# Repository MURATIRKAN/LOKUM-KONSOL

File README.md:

# LOKUM H1-H2 VE R1-R2-R3 VE R4 ARM LINUX VE ANDROID KONSOL PROJESİ 
MURAT IRKAN 2023-2024 
ANDROID 7.1 OYUN CS-GO: https://play.google.com/store/apps/details?id=com.tlb.csgo.offline&hl=en_GB
----------------------------------------------
MURAT IRKAN 2023-24 https://orangepi.com.tr/destek.html
----------------------------------------------

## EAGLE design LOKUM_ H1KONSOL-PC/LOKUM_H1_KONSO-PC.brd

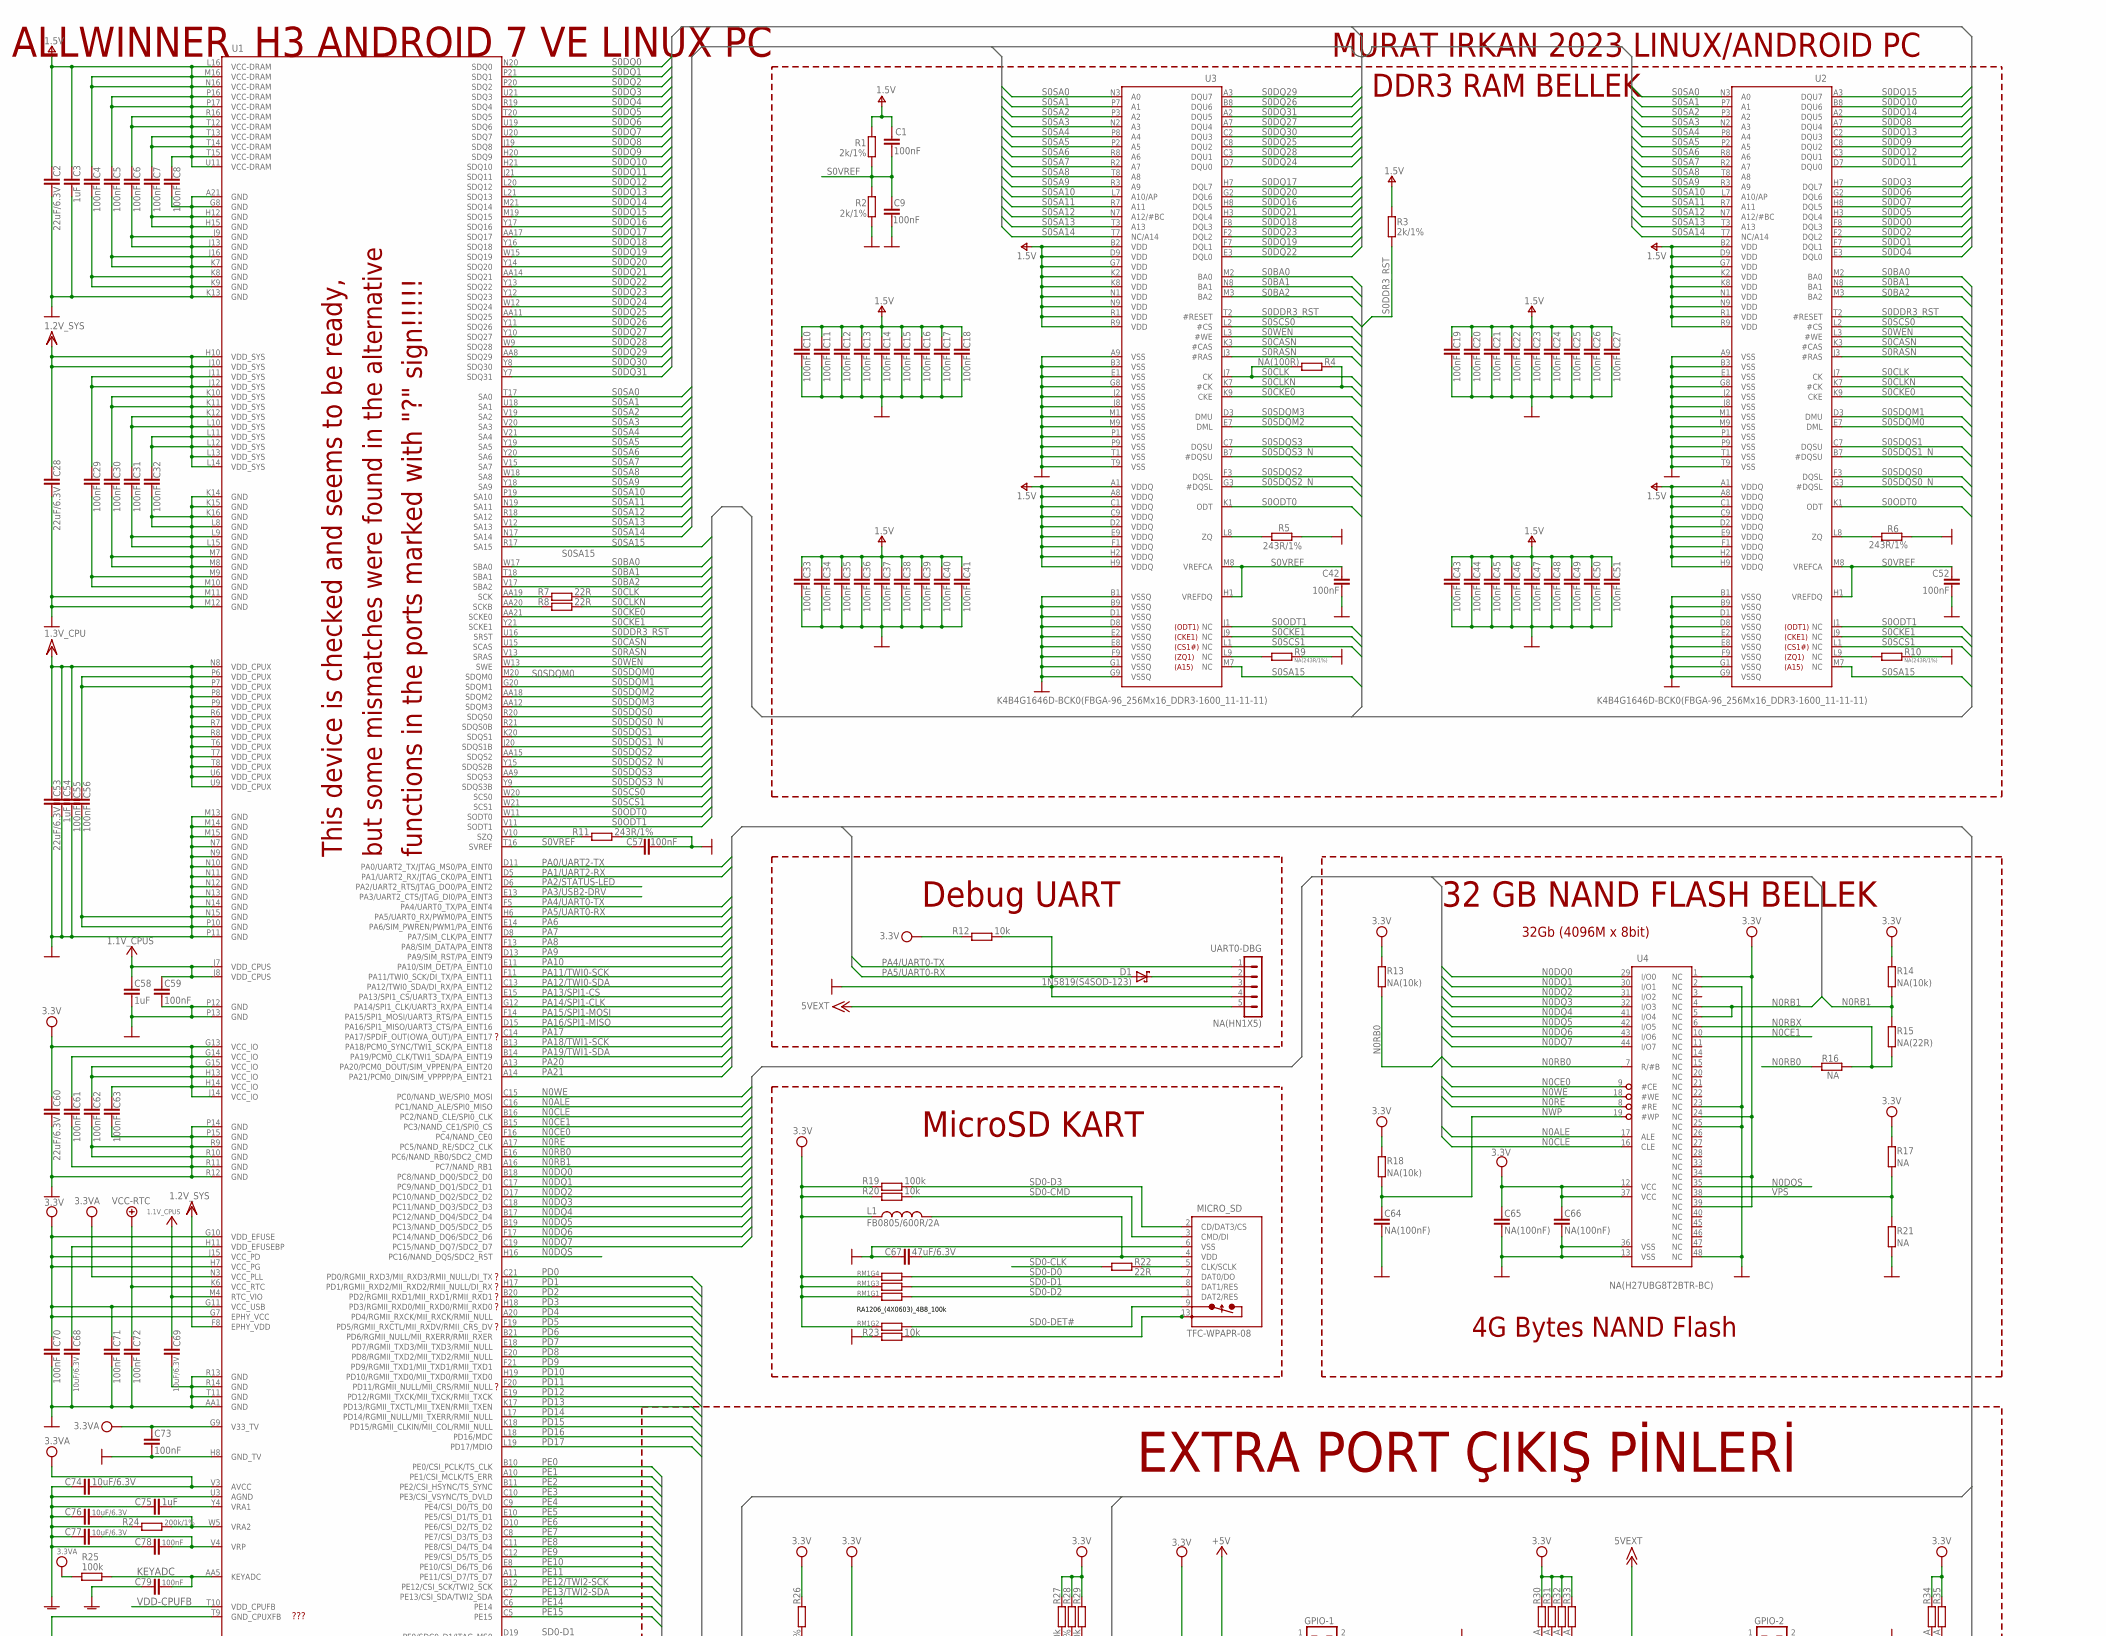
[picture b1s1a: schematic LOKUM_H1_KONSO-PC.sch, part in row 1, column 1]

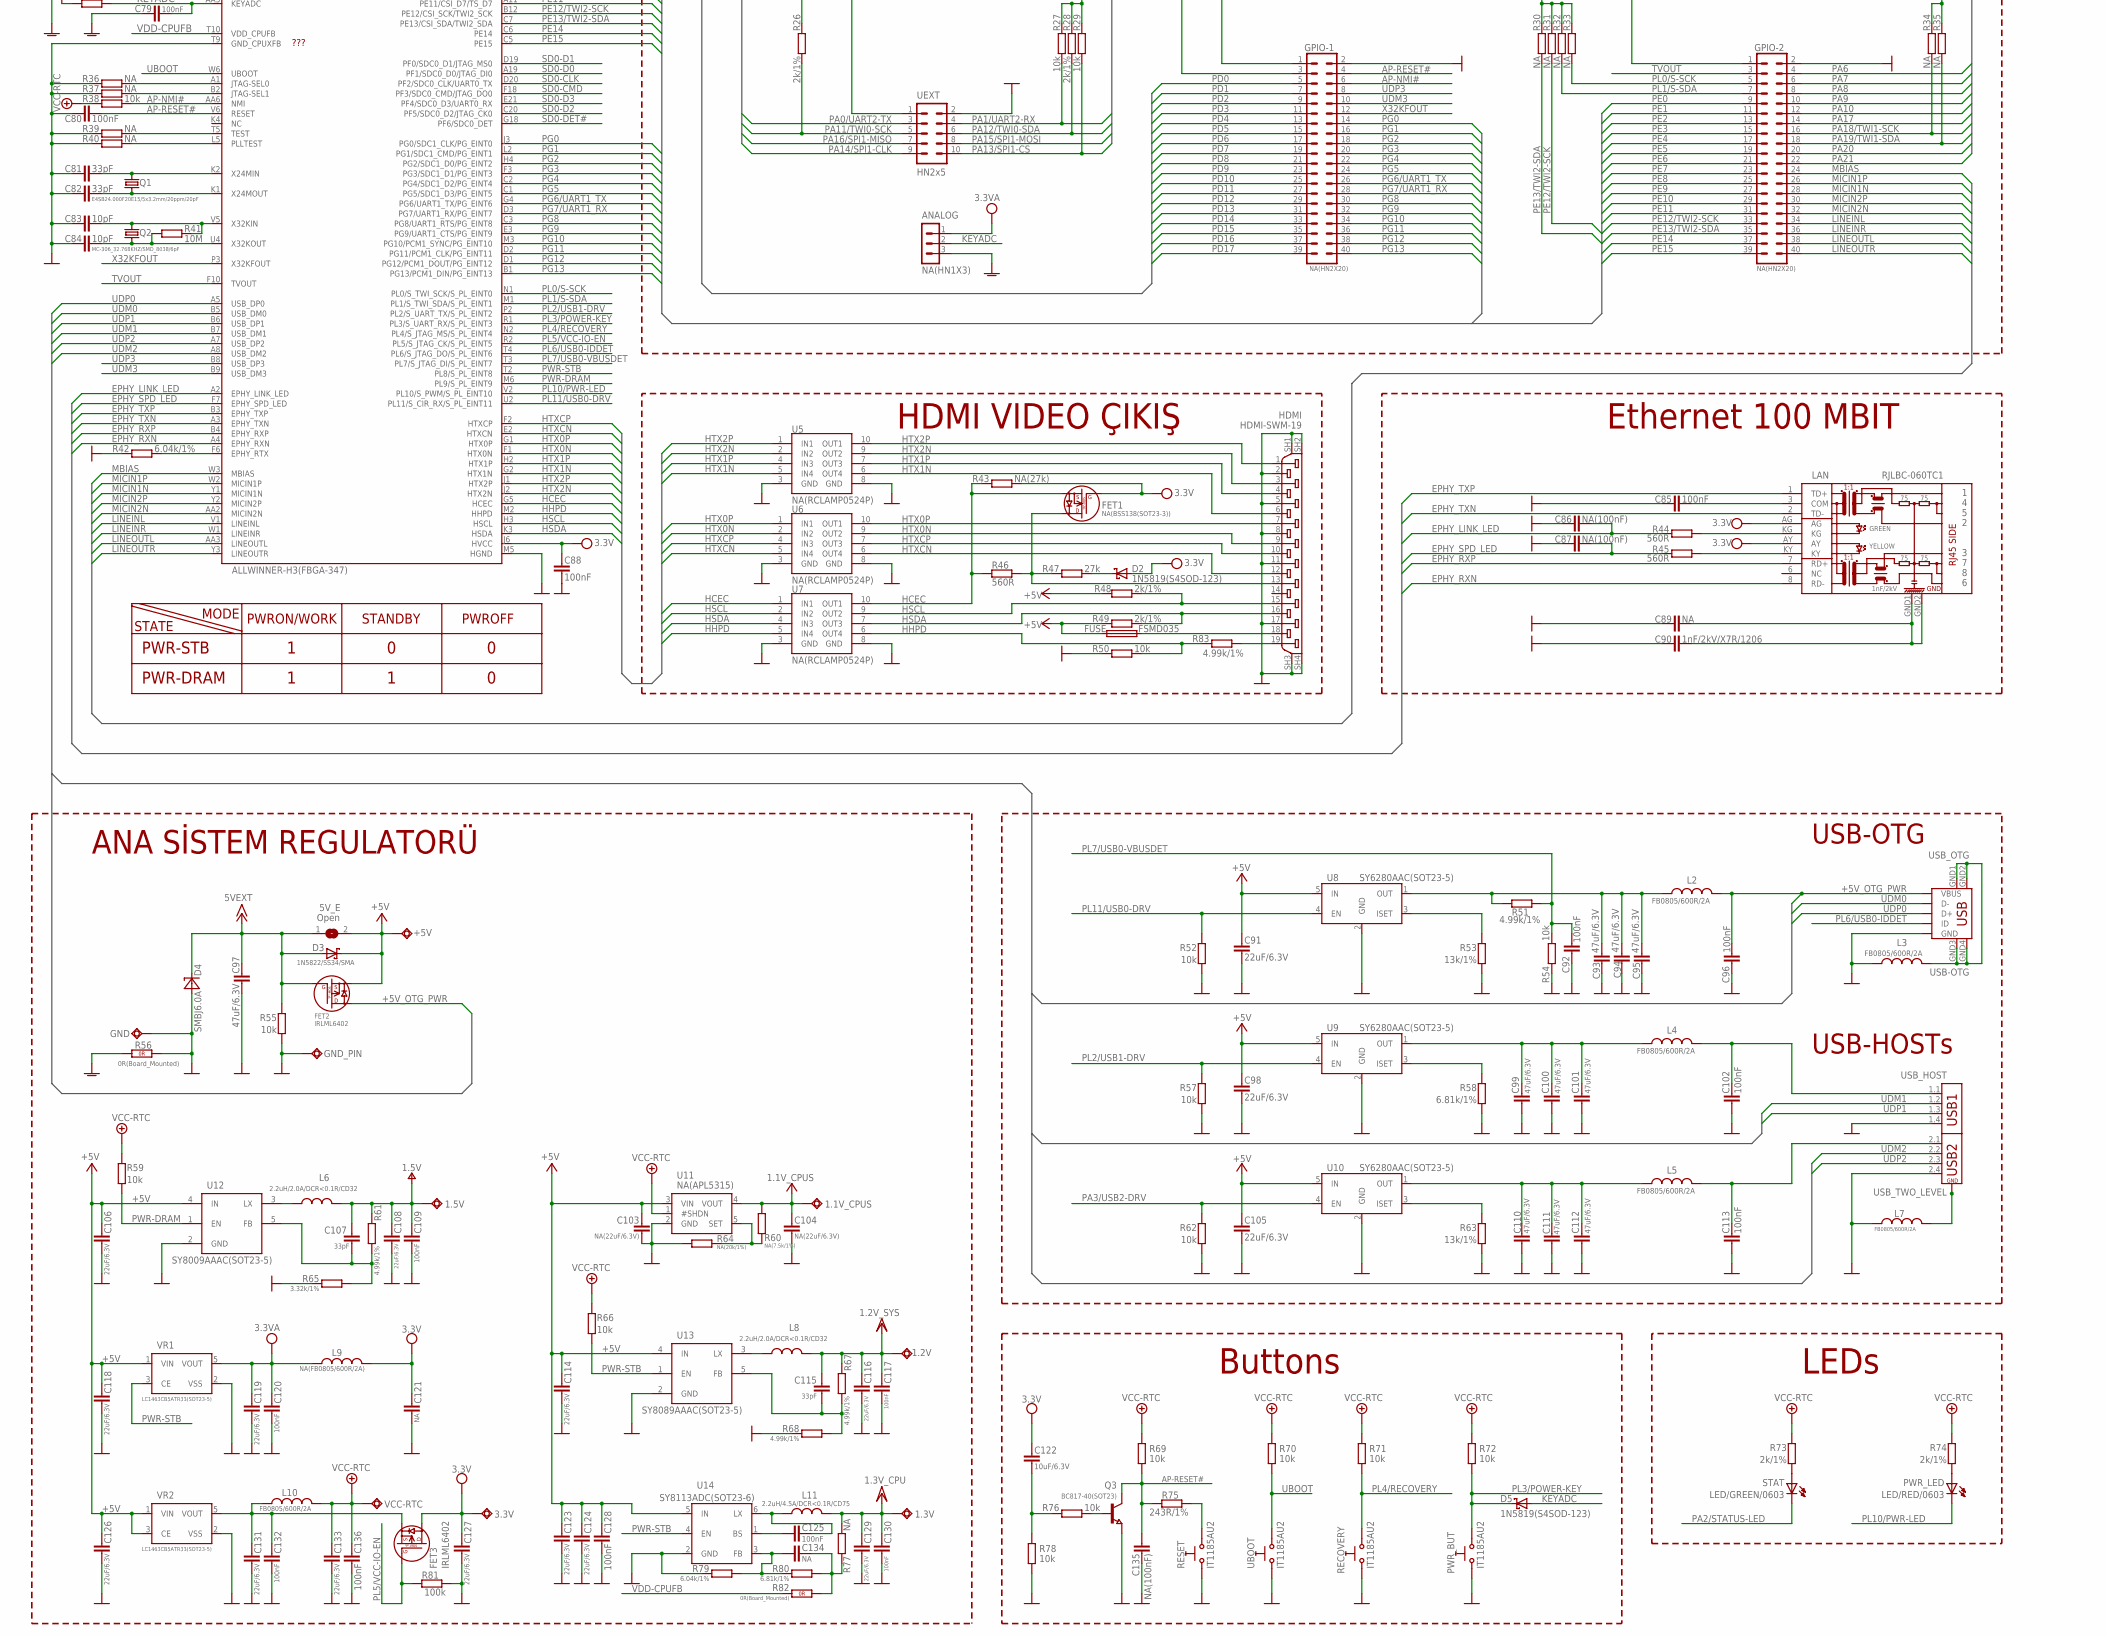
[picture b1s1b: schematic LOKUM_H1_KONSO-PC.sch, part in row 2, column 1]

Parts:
1.1V_CPUS, 1.2V, 1.3V, 1.5V, 3.3V: TESTPADTESTPAD_40-ROUND; TESTPAD_40-ROUND
5V_E: Open; SJ_1_SMALLER
+5V: TESTPADTESTPAD_40-ROUND; TESTPAD_40-ROUND
ANALOG: NA(HN1X3); HN1X3
C1, C4, C5, C6, C7, C8, C9, C10, C11, C12, C13, C14, C15, C16, C17, C18, C19, C20, C21, C22, C23, C24, C25, C26, C27, C29, C30, C31, C32, C33, C34, C35, C36, C37, C38, C39, C40, C41, C42, C43, C44, C45, C46, C47, C48, C49, C50, C51, C52, C55, C56, C57, C59, C61, C62, C63, C70, C71, C72, C73, C78, C79, C80, C85, C88, C92, C96, C102, C109, C113, C117, C120, C125, C128, C130, C132, C136: 100nF; C0402_TI
C2, C28, C53, C60, C91, C98, C105, C106, C108, C114, C116, C118, C119, C123, C124, C126, C127, C129, C131, C133: 22uF/6.3V; C0603_DWS
C3, C54, C58, C75: 1uF; C0603_DWS
C64, C65, C66, C86, C87, C135: NA(100nF); C0402_TI
C67, C93, C94, C95, C97, C99, C100, C101, C110, C111, C112: 47uF/6.3V; C0805_5MIL_DWS
C68, C69, C74, C76, C77, C122: 10uF/6.3V; C0603_DWS
C81, C82, C107, C115: 33pF; C0603_DWS
C83, C84: 10pF; C0603_DWS
C89: NA; C1206_5MILS_WS_ISO
C90: 1nF/2kV/X7R/1206; C1206_5MILS_WS_ISO
C103, C104: NA(22uF/6.3V); C0603_DWS
C121, C134: NA; C0603_DWS
D1, D2, D5: 1N5819(S4SOD-123); SOD-123
D3: 1N5822/SS34/SMA; MLL-41
D4: SMBJ6.0A; DO214AA
FET1: NA(BSS138(SOT23-3)); SOT23
FET2, FET3: IRLML6402; SOT23
FUSE: FSMD035; 1206
GND: TESTPADTESTPAD_40-ROUND; TESTPAD_40-ROUND
GND_PIN: TESTPAD3; TEST_PAD40/70/SQUARE
GPIO-1, GPIO-2: NA(HN2X20); HN2X20-MALE
HDMI: HDMI-SWM-19
L1, L2, L3, L4, L5, L7, L10: FB0805/600R/2A; L0805_5MIL_DWS
L6, L8: 2.2uH/2.0A/DCR<0.1R/CD32; CD32
L9: NA(FB0805/600R/2A); L0805_5MIL_DWS
L11: 2.2uH/4.5A/DCR<0.1R/CD75; CD73(75)
LAN: RJLBC-060TC1; RJLBC-060TC1_MILLING
MICRO_SD: TFC-WPAPR-08
PWR_BUT: IT1185AU2
PWR_LED: LED/RED/0603; LED-0603_TEST
Q1: E4SB24.000F20E15/5x3.2mm/20ppm/20pF; HCX-4S
Q2: MC-306_32.768KHZ/SMD_8038/6pF; MC-306
Q3: BC817-40(SOT23); SOT23
R1, R2, R3, R26, R28, R48, R49, R73, R74: 2k/1%; R0603_5MIL_DWS
R4: NA(100R); R0402_TI
R5, R6, R11, R75: 243R/1%; R0603_5MIL_DWS
R7, R8, R22: 22R; R0402_TI
R9, R10: NA(243R/1%); R0603_5MIL_DWS
R12, R20, R23, R27, R29, R38, R50, R52, R54, R55, R57, R59, R62, R66, R69, R70, R71, R72, R76, R78: 10k; R0603_5MIL_DWS
R13, R14, R18: NA(10k); R0603_5MIL_DWS
R15: NA(22R); R0402_TI
R16, R17, R21, R30, R31, R32, R33, R34, R35, R36, R37, R39, R40, R77: NA; R0603_5MIL_DWS
R19, R25, R81: 100k; R0603_5MIL_DWS
R24: 200k/1%; R0603_5MIL_DWS
R41: 10M; R0603_5MIL_DWS
R42, R79: 6.04k/1%; R0603_5MIL_DWS
R43: NA(27k); R0603_5MIL_DWS
R44, R45, R46: 560R; R0603_5MIL_DWS
R47: 27k; R0603_5MIL_DWS
R51, R61, R67, R68, R83: 4.99k/1%; R0603_5MIL_DWS
R53, R63: 13k/1%; R0603_5MIL_DWS
R56, R82: 0R(Board_Mounted); 0603_0R
R58, R80: 6.81k/1%; R0603_5MIL_DWS
R60: NA(7.5k/1%); R0603_5MIL_DWS
R64: NA(20k/1%); R0603_5MIL_DWS
R65: 3.32k/1%; R0603_5MIL_DWS
RECOVERY: IT1185AU2
RESET: IT1185AU2
RM1: RA1206_(4X0603)_4B8_100k; R_MATRIX_4
STAT: LED/GREEN/0603; LED-0603_TEST
U1: ALLWINNER-H3(FBGA-347); FBGA-347
U2, U3: K4B4G1646D-BCK0(FBGA-96_256Mx16_DDR3-1600_11-11-1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; FBGA96(HYNIX_SAMSUNG_512MX16_DDR3)
U4: NA(H27UBG8T2BTR-BC); TSOP48
U5, U6, U7: NA(RCLAMP0524P); SLP2510P8
U8, U9, U10: SY6280AAC(SOT23-5); SOT23-5
U11: NA(APL5315); SOT-23-5
U12: SY8009AAAC(SOT23-5); SOT23-5
U13: SY8089AAAC(SOT23-5); SOT23-5
U14: SY8113ADC(SOT23-6); SOT23-6
UART0-DBG: NA(HN1X5); HN1X5
UBOOT: IT1185AU2
UEXT: HN2x5; ML10_NEW
USB_HOST: USB_TWO_LEVEL
USB_OTG: USB-OTG; USB_MINI_9PIN
VCC-RTC: TESTPADTESTPAD_40-ROUND; TESTPAD_40-ROUND
VR1, VR2: LC1463CB5ATR33(SOT23-5); SOT-23-5

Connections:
+5V: 5V_E.2, +5V.1, C91.1, C98.1, C103.1, C105.1, C106.1, C114.1, C118.1, C123.1, C124.1, C126.1, C128.2, D3.K (C), FET2.2 (S), FUSE.1, GPIO-1.1, R48.2, R49.2, U8.5 (IN), U9.5 (IN), U10.5 (IN), U11.3 (VIN), U12.4 (IN), U13.4 (IN), U14.5 (IN), VR1.1 (VIN), VR2.1 (VIN), VR2.3 (CE)
+5V_OTG_PWR: C96.1, FET2.3 (D), L2.1, USB_OTG.VBUS
+7V: C72.2, C133.1, C136.2, L10.2, R38.2, R59.1, R66.1, R69.1, R70.1, R71.1, R72.1, R73.1, R74.1, U1.K6 (VCC_RTC), U11.1 (#SHDN), VCC-RTC.1
+15V: 5V_E.1, C97.1, D3.A, D4.C, FET2.1 (G), GPIO-2.1, R55.2, UART0-DBG.5
AP-NMI#: GPIO-1.6, R38.1, U1.AA6 (NMI)
AP-RESET#: C80.2, C135.2, GPIO-1.4, Q3.3 (C), R69.2, R75.2, U1.V6 (RESET)
EPHY_LINK_LED: C86.2, R44.2, U1.A2 (EPHY_LINK_LED)
EPHY_RXN: LAN.8 (RD-), U1.A4 (EPHY_RXN)
EPHY_RXP: LAN.7 (RD+), U1.B4 (EPHY_RXP)
EPHY_SPD_LED: C87.2, R45.2, U1.F7 (EPHY_SPD_LED)
EPHY_TXN: LAN.2 (TD-), U1.A3 (EPHY_TXN)
EPHY_TXP: LAN.1 (TD+), U1.B3 (EPHY_TXP)
GND: C2.2, C3.2, C4.1, C5.1, C6.1, C7.1, C8.1, C9.1, C10.1, C11.1, C12.1, C13.1, C14.1, C15.1, C16.1, C17.1, C18.1, C19.1, C20.1, C21.1, C22.1, C23.1, C24.1, C25.1, C26.1, C27.1, C28.2, C29.1, C30.1, C31.1, C32.1, C33.1, C34.1, C35.1, C36.1, C37.1, C38.1, C39.1, C40.1, C41.1, C42.1, C43.1, C44.1, C45.1, C46.1, C47.1, C48.1, C49.1, C50.1, C51.1, C52.1, C53.2, C54.2, C55.1, C56.1, C57.1, C58.2, C59.1, C60.2, C61.1, C62.1, C63.1, C64.1, C65.1, C66.1, C67.1, C68.2, C69.2, C70.1, C71.1, C72.1, C73.1, C80.1, C81.1, C82.1, C83.1, C84.1, C85.1, C86.1, C87.1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
GNDA: ANALOG.3, C74.1, C75.1, C76.1, C77.1, C78.1, C79.1, R24.2, R56.2 (1.2), U1.U3 (AGND)
HCEC: FET1.2 (S), R43.1, R46.2, U1.G5 (HCEC), U7.1 (IN1), U7.10 (OUT1)
HDMI_5V_SOURCE: FUSE.2, HDMI.18
HHPD: R50.1, R83.1, U1.M2 (HHPD), U7.5 (IN4), U7.6 (OUT4)
HSCL: HDMI.15, R48.1, U1.H3 (HSCL), U7.2 (IN2), U7.9 (OUT2)
HSDA: HDMI.16, R49.1, U1.K3 (HSDA), U7.4 (IN3), U7.7 (OUT3)
HTX0N: HDMI.9, U1.F1 (HTX0N), U6.2 (IN2), U6.9 (OUT2)
HTX0P: HDMI.7, U1.G1 (HTX0P), U6.1 (IN1), U6.10 (OUT1)
HTX1N: HDMI.6, U1.G2 (HTX1N), U5.5 (IN4), U5.6 (OUT4)
HTX1P: HDMI.4, U1.H2 (HTX1P), U5.4 (IN3), U5.7 (OUT3)
HTX2N: HDMI.3, U1.J2 (HTX2N), U5.2 (IN2), U5.9 (OUT2)
HTX2P: HDMI.1, U1.J1 (HTX2P), U5.1 (IN1), U5.10 (OUT1)
HTXCN: HDMI.12, U1.E2 (HTXCN), U6.5 (IN4), U6.6 (OUT4)
HTXCP: HDMI.10, U1.F2 (HTXCP), U6.4 (IN3), U6.7 (OUT3)
KEYADC: ANALOG.2, C79.2, D5.A, R25.1, U1.AA5 (KEYADC)
LINEINL: GPIO-2.34, U1.V1 (LINEINL)
LINEINR: GPIO-2.36, U1.W1 (LINEINR)
LINEOUTL: GPIO-2.38, U1.AA3 (LINEOUTL)
LINEOUTR: GPIO-2.40, U1.Y3 (LINEOUTR)
MBIAS: GPIO-2.24, U1.W3 (MBIAS)
MICIN1N: GPIO-2.28, U1.Y1 (MICIN1N)
MICIN1P: GPIO-2.26, U1.W2 (MICIN1P)
MICIN2N: GPIO-2.32, U1.AA2 (MICIN2N)
MICIN2P: GPIO-2.30, U1.Y2 (MICIN2P)
N0ALE: U1.C16 (PC1/NAND_ALE/SPI0_MISO), U4.17 (ALE)
N0CE0: U1.F16 (PC4/NAND_CE0), U4.9 (#CE)
N0CE1: U1.B15 (PC3/NAND_CE1/SPI0_CS), U4.10 (NC)
N0CLE: U1.B16 (PC2/NAND_CLE/SPI0_CLK), U4.16 (CLE)
N0DQ0: U1.B18 (PC8/NAND_DQ0/SDC2_D0), U4.29 (I/O0)
N0DQ1: U1.C17 (PC9/NAND_DQ1/SDC2_D1), U4.30 (I/O1)
N0DQ2: U1.D17 (PC10/NAND_DQ2/SDC2_D2), U4.31 (I/O2)
N0DQ3: U1.C18 (PC11/NAND_DQ3/SDC2_D3), U4.32 (I/O3)
N0DQ4: U1.B17 (PC12/NAND_DQ4/SDC2_D4), U4.41 (I/O4)
N0DQ5: U1.B19 (PC13/NAND_DQ5/SDC2_D5), U4.42 (I/O5)
N0DQ6: U1.F17 (PC14/NAND_DQ6/SDC2_D6), U4.43 (I/O6)
N0DQ7: U1.C19 (PC15/NAND_DQ7/SDC2_D7), U4.44 (I/O7)
N0DQS: U1.H16 (PC16/NAND_DQS/SDC2_RST), U4.35 (NC)
N0RB0: R13.2, R16.2, U1.E16 (PC6/NAND_RB0/SDC2_CMD), U4.7 (R/#B)
N0RB1: R14.2, R15.1, U1.A16 (PC7/NAND_RB1), U4.4 (NC), U4.5 (NC)
N0RBX: R15.2, R16.1, U4.6 (NC)
N0RE: U1.A17 (PC5/NAND_RE/SDC2_CLK), U4.8 (#RE)
N0WE: U1.C15 (PC0/NAND_WE/SPI0_MOSI), U4.18 (#WE)
unnamed: MICRO_SD.5 (CLK/SCLK), R22.1
unnamed: R11.2, U1.V10 (SZQ)
unnamed: R5.2, U3.L8 (ZQ)
unnamed: D2.C, R47.1
unnamed: R6.2, U2.L8 (ZQ)
unnamed: R9.2, U3.L9 (NC)
unnamed: D1.C, UART0-DBG.2
unnamed: R7.2, U1.AA19 (SCK)
unnamed: R8.2, U1.AA20 (SCKB)
unnamed: R37.1, U1.B2 (JTAG-SEL1)
unnamed: R10.2, U2.L9 (NC)
unnamed: L3.2, USB_OTG.GND1, USB_OTG.GND2, USB_OTG.GND3, USB_OTG.GND4
unnamed: HDMI.19, R83.2
unnamed: C75.2, U1.Y4 (VRA1)
unnamed: R53.2, U8.3 (ISET)
unnamed: R75.1, RESET.1 (0)
unnamed: C93.1, C94.1, C95.1, L2.2, R51.2, U8.1 (OUT)
unnamed: FET1.3 (D), HDMI.13, R46.1, R47.2
unnamed: Q3.1 (B), R76.2
unnamed: C89.2, C90.2, LAN.GND1, LAN.GND2
unnamed: L6.1, U12.3 (LX)
unnamed: R36.1, U1.A1 (JTAG-SEL0)
unnamed: R39.1, U1.T5 (TEST)
unnamed: R60.2, R64.2, U11.5 (SET)
unnamed: R40.1, U1.L5 (PLLTEST)
unnamed: C107.2, R61.2, R65.1, U12.5 (FB)
unnamed: C122.2, R76.1, R78.1
unnamed: C125.2, U14.1 (BS)
unnamed: L8.1, U13.3 (LX)
unnamed: C115.2, R67.2, R68.1, U13.5 (FB)
unnamed: C125.1, L11.1, U14.6 (LX)
unnamed: PWR_LED.A, R74.2
unnamed: C134.2, R79.1, R80.1, U14.3 (FB)
unnamed: LAN.KG, R44.1
unnamed: R42.1, U1.F6 (EPHY_RTX)
unnamed: C85.2, LAN.3 (COM)
unnamed: LAN.KY, R45.1
unnamed: MICRO_SD.10 (PACK1), MICRO_SD.11 (PACK2), MICRO_SD.12 (PACK3), MICRO_SD.13 (PACK4), R23.1
unnamed: C131.1, C132.1, FET3.2 (S), L10.1, VR2.5 (VOUT)
unnamed: C83.2, Q2.4 (2), R41.1, U1.V5 (X32KIN)
unnamed: R58.2, U9.3 (ISET)
unnamed: C102.1, L4.2, USB_HOST.1.1
unnamed: C84.2, Q2.1, R41.2, U1.U4 (X32KOUT)
unnamed: C77.2, C78.2, U1.V4 (VRP)
unnamed: R63.2, U10.3 (ISET)
unnamed: C76.2, R24.1, U1.W5 (VRA2)
unnamed: C99.1, C100.1, C101.1, L4.1, U9.1 (OUT)
unnamed: L7.2, USB_HOST.GND1, USB_HOST.GND2, USB_HOST.GND3, USB_HOST.GND4
unnamed: C113.1, L5.2, USB_HOST.2.1
unnamed: C110.1, C111.1, C112.1, L5.1, U10.1 (OUT)
unnamed: R73.2, STAT.A
NWP: C64.2, R18.2, U4.19 (#WP)
PA0/UART2-TX: U1.D11 (PA0/UART2_TX/JTAG_MS0/PA_EINT0), UEXT.3
PA1/UART2-RX: R27.2, U1.D5 (PA1/UART2_RX/JTAG_CK0/PA_EINT1), UEXT.4
PA2/STATUS-LED: STAT.C, U1.D6 (PA2/UART2_RTS/JTAG_DO0/PA_EINT2)
PA3/USB2-DRV: R62.2, U1.E13 (PA3/UART2_CTS/JTAG_DI0/PA_EINT3), U10.4 (EN)
PA4/UART0-TX: U1.F5 (PA4/UART0_TX/PA_EINT4), UART0-DBG.1
PA5/UART0-RX: D1.A, R12.1, U1.H6 (PA5/UART0_RX/PWM0/PA_EINT5)
PA6: GPIO-2.4, U1.E14 (PA6/SIM_PWREN/PWM1/PA_EINT6)
PA7: GPIO-2.6, U1.D8 (PA7/SIM_CLK/PA_EINT7)
PA8: GPIO-2.8, U1.F13 (PA8/SIM_DATA/PA_EINT8)
PA9: GPIO-2.10, U1.D13 (PA9/SIM_RST/PA_EINT9)
PA10: GPIO-2.12, U1.E11 (PA10/SIM_DET/PA_EINT10)
PA11/TWI0-SCK: R26.2, U1.F11 (PA11/TWI0_SCK/DI_TX/PA_EINT11), UEXT.5
PA12/TWI0-SDA: R28.2, U1.C13 (PA12/TWI0_SDA/DI_RX/PA_EINT12), UEXT.6
PA13/SPI1-CS: R29.2, U1.E15 (PA13/SPI1_CS/UART3_TX/PA_EINT13), UEXT.10
PA14/SPI1-CLK: U1.G12 (PA14/SPI1_CLK/UART3_RX/PA_EINT14), UEXT.9
PA15/SPI1-MOSI: U1.F14 (PA15/SPI1_MOSI/UART3_RTS/PA_EINT15), UEXT.8
PA16/SPI1-MISO: U1.D15 (PA16/SPI1_MISO/UART3_CTS/PA_EINT16), UEXT.7
PA17: GPIO-2.14, U1.C14 (PA17/SPDIF_OUT(OWA_OUT)/PA_EINT17)
PA18/TWI1-SCK: GPIO-2.16, R34.2, U1.B13 (PA18/PCM0_SYNC/TWI1_SCK/PA_EINT18)
PA19/TWI1-SDA: GPIO-2.18, R35.2, U1.B14 (PA19/PCM0_CLK/TWI1_SDA/PA_EINT19)
PA20: GPIO-2.20, U1.A13 (PA20/PCM0_DOUT/SIM_VPPEN/PA_EINT20)
PA21: GPIO-2.22, U1.A14 (PA21/PCM0_DIN/SIM_VPPPP/PA_EINT21)
PD0: GPIO-1.5, U1.C21 (PD0/RGMII_RXD3/MII_RXD3/RMII_NULL/DI_TX)
PD1: GPIO-1.7, U1.H17 (PD1/RGMII_RXD2/MII_RXD2/RMII_NULL/DI_RX)
PD2: GPIO-1.9, U1.B20 (PD2/RGMII_RXD1/MII_RXD1/RMII_RXD1)
PD3: GPIO-1.11, U1.H18 (PD3/RGMII_RXD0/MII_RXD0/RMII_RXD0)
PD4: GPIO-1.13, U1.A20 (PD4/RGMII_RXCK/MII_RXCK/RMII_NULL)
PD5: GPIO-1.15, U1.F19 (PD5/RGMII_RXCTL/MII_RXDV/RMII_CRS_DV)
PD6: GPIO-1.17, U1.B21 (PD6/RGMII_NULL/MII_RXERR/RMII_RXER)
PD7: GPIO-1.19, U1.E18 (PD7/RGMII_TXD3/MII_TXD3/RMII_NULL)
PD8: GPIO-1.21, U1.E20 (PD8/RGMII_TXD2/MII_TXD2/RMII_NULL)
PD9: GPIO-1.23, U1.F21 (PD9/RGMII_TXD1/MII_TXD1/RMII_TXD1)
PD10: GPIO-1.25, U1.H19 (PD10/RGMII_TXD0/MII_TXD0/RMII_TXD0)
PD11: GPIO-1.27, U1.F20 (PD11/RGMII_NULL/MII_CRS/RMII_NULL)
PD12: GPIO-1.29, U1.E19 (PD12/RGMII_TXCK/MII_TXCK/RMII_TXCK)
PD13: GPIO-1.31, U1.K17 (PD13/RGMII_TXCTL/MII_TXEN/RMII_TXEN)
PD14: GPIO-1.33, U1.L17 (PD14/RGMII_NULL/MII_TXERR/RMII_NULL)
PD15: GPIO-1.35, U1.K18 (PD15/RGMII_CLKIN/MII_COL/RMII_NULL)
PD16: GPIO-1.37, U1.L18 (PD16/MDC)
PD17: GPIO-1.39, U1.L19 (PD17/MDIO)
PE0: GPIO-2.9, U1.B10 (PE0/CSI_PCLK/TS_CLK)
PE1: GPIO-2.11, U1.A10 (PE1/CSI_MCLK/TS_ERR)
PE2: GPIO-2.13, U1.B11 (PE2/CSI_HSYNC/TS_SYNC)
PE3: GPIO-2.15, U1.C10 (PE3/CSI_VSYNC/TS_DVLD)
PE4: GPIO-2.17, U1.C9 (PE4/CSI_D0/TS_D0)
PE5: GPIO-2.19, U1.E10 (PE5/CSI_D1/TS_D1)
PE6: GPIO-2.21, U1.D10 (PE6/CSI_D2/TS_D2)
PE7: GPIO-2.23, U1.C8 (PE7/CSI_D3/TS_D3)
PE8: GPIO-2.25, U1.C11 (PE8/CSI_D4/TS_D4)
PE9: GPIO-2.27, U1.C12 (PE9/CSI_D5/TS_D5)
PE10: GPIO-2.29, U1.E8 (PE10/CSI_D6/TS_D6)
PE11: GPIO-2.31, U1.A11 (PE11/CSI_D7/TS_D7)
PE12/TWI2-SCK: GPIO-2.33, R31.2, U1.B12 (PE12/CSI_SCK/TWI2_SCK)
PE13/TWI2-SDA: GPIO-2.35, R30.2, U1.C7 (PE13/CSI_SDA/TWI2_SDA)
PE14: GPIO-2.37, U1.C6 (PE14)
PE15: GPIO-2.39, U1.C5 (PE15)
PG0: GPIO-1.14, U1.J3 (PG0/SDC1_CLK/PG_EINT0)
PG1: GPIO-1.16, U1.L2 (PG1/SDC1_CMD/PG_EINT1)
PG2: GPIO-1.18, U1.H4 (PG2/SDC1_D0/PG_EINT2)
PG3: GPIO-1.20, U1.F3 (PG3/SDC1_D1/PG_EINT3)
PG4: GPIO-1.22, U1.C2 (PG4/SDC1_D2/PG_EINT4)
PG5: GPIO-1.24, U1.C1 (PG5/SDC1_D3/PG_EINT5)
PG6/UART1_TX: GPIO-1.26, U1.G4 (PG6/UART1_TX/PG_EINT6)
PG7/UART1_RX: GPIO-1.28, U1.D3 (PG7/UART1_RX/PG_EINT7)
PG8: GPIO-1.30, U1.C3 (PG8/UART1_RTS/PG_EINT8)
PG9: GPIO-1.32, U1.E3 (PG9/UART1_CTS/PG_EINT9)
PG10: GPIO-1.34, U1.M3 (PG10/PCM1_SYNC/PG_EINT10)
PG11: GPIO-1.36, U1.D2 (PG11/PCM1_CLK/PG_EINT11)
PG12: GPIO-1.38, U1.D1 (PG12/PCM1_DOUT/PG_EINT12)
PG13: GPIO-1.40, U1.B1 (PG13/PCM1_DIN/PG_EINT13)
PL0/S-SCK: GPIO-2.5, R33.2, U1.N1 (PL0/S_TWI_SCK/S_PL_EINT0)
PL1/S-SDA: GPIO-2.7, R32.2, U1.M1 (PL1/S_TWI_SDA/S_PL_EINT1)
PL2/USB1-DRV: R57.2, U1.P2 (PL2/S_UART_TX/S_PL_EINT2), U9.4 (EN)
PL3/POWER-KEY: D5.C, PWR_BUT.1 (0), R72.2, U1.R1 (PL3/S_UART_RX/S_PL_EINT3)
PL4/RECOVERY: R71.2, RECOVERY.1 (0), U1.N2 (PL4/S_JTAG_MS/S_PL_EINT4)
PL5/VCC-IO-EN: FET3.1 (G), R81.1, U1.R2 (PL5/S_JTAG_CK/S_PL_EINT5)
PL6/USB0-IDDET: U1.T4 (PL6/S_JTAG_DO/S_PL_EINT6), USB_OTG.ID
PL7/USB0-VBUSDET: C92.1, R51.1, R54.2, U1.T3 (PL7/S_JTAG_DI/S_PL_EINT7)
PL10/PWR-LED: PWR_LED.C, U1.V2 (PL10/S_PWM/S_PL_EINT10)
PL11/USB0-DRV: R52.2, U1.U2 (PL11/S_CIR_RX/S_PL_EINT11), U8.4 (EN)
PWR-DRAM: R59.2, U1.M6 (PL9/S_PL_EINT9), U12.1 (EN)
PWR-STB: R66.2, U1.T2 (PL8/S_PL_EINT8), U13.1 (EN), U14.4 (EN), VR1.3 (CE)
S0BA0: U1.W17 (SBA0), U2.M2 (BA0), U3.M2 (BA0)
S0BA1: U1.T18 (SBA1), U2.N8 (BA1), U3.N8 (BA1)
S0BA2: U1.V17 (SBA2), U2.M3 (BA2), U3.M3 (BA2)
S0CASN: U1.U15 (SCAS), U2.K3 (#CAS), U3.K3 (#CAS)
S0CKE0: U1.AA21 (SCKE0), U2.K9 (CKE), U3.K9 (CKE)
S0CKE1: U1.Y21 (SCKE1), U2.J9 (NC), U3.J9 (NC)
S0CLK: R4.2, R7.1, U2.J7 (CK), U3.J7 (CK)
S0CLKN: R4.1, R8.1, U2.K7 (#CK), U3.K7 (#CK)
S0DDR3_RST: R3.1, U1.U16 (SRST), U2.T2 (#RESET), U3.T2 (#RESET)
S0DQ0: U1.N20 (SDQ0), U2.F8 (DQL3)
S0DQ1: U1.P21 (SDQ1), U2.F7 (DQL1)
S0DQ2: U1.P20 (SDQ2), U2.F2 (DQL2)
S0DQ3: U1.U21 (SDQ3), U2.H7 (DQL7)
S0DQ4: U1.R19 (SDQ4), U2.E3 (DQL0)
S0DQ5: U1.T20 (SDQ5), U2.H3 (DQL4)
S0DQ6: U1.U19 (SDQ6), U2.G2 (DQL6)
S0DQ7: U1.U20 (SDQ7), U2.H8 (DQL5)
S0DQ8: U1.J19 (SDQ8), U2.A7 (DQU4)
S0DQ9: U1.H20 (SDQ9), U2.C8 (DQU2)
S0DQ10: U1.H21 (SDQ10), U2.B8 (DQU6)
S0DQ11: U1.J21 (SDQ11), U2.D7 (DQU0)
S0DQ12: U1.L20 (SDQ12), U2.C3 (DQU1)
S0DQ13: U1.L21 (SDQ13), U2.C2 (DQU3)
S0DQ14: U1.M21 (SDQ14), U2.A2 (DQU5)
S0DQ15: U1.M19 (SDQ15), U2.A3 (DQU7)
S0DQ16: U1.Y17 (SDQ16), U3.H8 (DQL5)
S0DQ17: U1.AA17 (SDQ17), U3.H7 (DQL7)
S0DQ18: U1.Y16 (SDQ18), U3.F8 (DQL3)
S0DQ19: U1.W15 (SDQ19), U3.F7 (DQL1)
S0DQ20: U1.Y14 (SDQ20), U3.G2 (DQL6)
S0DQ21: U1.AA14 (SDQ21), U3.H3 (DQL4)
S0DQ22: U1.Y13 (SDQ22), U3.E3 (DQL0)
S0DQ23: U1.Y12 (SDQ23), U3.F2 (DQL2)
S0DQ24: U1.W12 (SDQ24), U3.D7 (DQU0)
S0DQ25: U1.AA11 (SDQ25), U3.C8 (DQU2)
S0DQ26: U1.Y11 (SDQ26), U3.B8 (DQU6)
S0DQ27: U1.Y10 (SDQ27), U3.A7 (DQU4)
S0DQ28: U1.W9 (SDQ28), U3.C3 (DQU1)
S0DQ29: U1.AA8 (SDQ29), U3.A3 (DQU7)
S0DQ30: U1.Y8 (SDQ30), U3.C2 (DQU3)
S0DQ31: U1.Y7 (SDQ31), U3.A2 (DQU5)
S0ODT0: U1.W11 (SODT0), U2.K1 (ODT), U3.K1 (ODT)
S0ODT1: U1.V11 (SODT1), U2.J1 (NC), U3.J1 (NC)
S0RASN: U1.V13 (SRAS), U2.J3 (#RAS), U3.J3 (#RAS)
S0SA0: U1.T17 (SA0), U2.N3 (A0), U3.N3 (A0)
S0SA1: U1.U18 (SA1), U2.P7 (A1), U3.P7 (A1)
S0SA2: U1.V19 (SA2), U2.P3 (A2), U3.P3 (A2)
S0SA3: U1.V20 (SA3), U2.N2 (A3), U3.N2 (A3)
S0SA4: U1.V21 (SA4), U2.P8 (A4), U3.P8 (A4)
S0SA5: U1.Y19 (SA5), U2.P2 (A5), U3.P2 (A5)
S0SA6: U1.Y20 (SA6), U2.R8 (A6), U3.R8 (A6)
S0SA7: U1.V15 (SA7), U2.R2 (A7), U3.R2 (A7)
S0SA8: U1.W18 (SA8), U2.T8 (A8), U3.T8 (A8)
S0SA9: U1.Y18 (SA9), U2.R3 (A9), U3.R3 (A9)
S0SA10: U1.P19 (SA10), U2.L7 (A10/AP), U3.L7 (A10/AP)
S0SA11: U1.N19 (SA11), U2.R7 (A11), U3.R7 (A11)
S0SA12: U1.R18 (SA12), U2.N7 (A12/#BC), U3.N7 (A12/#BC)
S0SA13: U1.V12 (SA13), U2.T3 (A13), U3.T3 (A13)
S0SA14: U1.N17 (SA14), U2.T7 (NC/A14), U3.T7 (NC/A14)
S0SA15: U1.R17 (SA15), U2.M7 (NC), U3.M7 (NC)
S0SCS0: U1.W20 (SCS0), U2.L2 (#CS), U3.L2 (#CS)
S0SCS1: U1.W21 (SCS1), U2.L1 (NC), U3.L1 (NC)
S0SDQM0: U1.M20 (SDQM0), U2.E7 (DML)
S0SDQM1: U1.G20 (SDQM1), U2.D3 (DMU)
S0SDQM2: U1.AA18 (SDQM2), U3.E7 (DML)
S0SDQM3: U1.AA12 (SDQM3), U3.D3 (DMU)
S0SDQS0: U1.R20 (SDQS0), U2.F3 (DQSL)
S0SDQS0_N: U1.R21 (SDQS0B), U2.G3 (#DQSL)
S0SDQS1: U1.K20 (SDQS1), U2.C7 (DQSU)
S0SDQS1_N: U1.J20 (SDQS1B), U2.B7 (#DQSU)
S0SDQS2: U1.AA15 (SDQS2), U3.F3 (DQSL)
S0SDQS2_N: U1.Y15 (SDQS2B), U3.G3 (#DQSL)
S0SDQS3: U1.AA9 (SDQS3), U3.C7 (DQSU)
S0SDQS3_N: U1.Y9 (SDQS3B), U3.B7 (#DQSU)
S0VREF: C1.2, C9.2, C42.2, C52.2, C57.2, R1.1, R2.2, U1.T16 (SVREF), U2.H1 (VREFDQ), U2.M8 (VREFCA), U3.H1 (VREFDQ), U3.M8 (VREFCA)
S0WEN: U1.W13 (SWE), U2.L3 (#WE), U3.L3 (#WE)
SD0-CLK: R22.2, U1.D20 (PF2/SDC0_CLK/UART0_TX)
SD0-CMD: MICRO_SD.3 (CMD/DI), R20.1, U1.F18 (PF3/SDC0_CMD/JTAG_DO0)
SD0-D0: MICRO_SD.7 (DAT0/DO), RM1.4.1 (1), U1.A19 (PF1/SDC0_D0/JTAG_DI0)
SD0-D1: MICRO_SD.8 (DAT1/RES), RM1.3.1 (1), U1.D19 (PF0/SDC0_D1/JTAG_MS0)
SD0-D2: MICRO_SD.1 (DAT2/RES), RM1.1.1 (1), U1.C20 (PF5/SDC0_D2/JTAG_CK0)
SD0-D3: MICRO_SD.2 (CD/DAT3/CS), R19.1, U1.E21 (PF4/SDC0_D3/UART0_RX)
SD0-DET#: MICRO_SD.9 (CP_E), RM1.2.1 (1), U1.G18 (PF6/SDC0_DET)
SD_VCC: C67.2, L1.2, MICRO_SD.4 (VDD)
TVOUT: GPIO-2.3, U1.F10 (TVOUT)
UBOOT: R70.2, U1.W6 (UBOOT), UBOOT.1 (0)
UDM0: U1.B5 (USB_DM0), USB_OTG.D-
UDM1: U1.B7 (USB_DM1), USB_HOST.1.2
UDM2: U1.A8 (USB_DM2), USB_HOST.2.2
UDM3: GPIO-1.10, U1.B9 (USB_DM3)
UDP0: U1.A5 (USB_DP0), USB_OTG.D+
UDP1: U1.B6 (USB_DP1), USB_HOST.1.3
UDP2: U1.A7 (USB_DP2), USB_HOST.2.3
UDP3: GPIO-1.8, U1.B8 (USB_DP3)
V+: 1.5V.1, C1.1, C2.1, C3.1, C4.2, C5.2, C6.2, C7.2, C8.2, C10.2, C11.2, C12.2, C13.2, C14.2, C15.2, C16.2, C17.2, C18.2, C19.2, C20.2, C21.2, C22.2, C23.2, C24.2, C25.2, C26.2, C27.2, C33.2, C34.2, C35.2, C36.2, C37.2, C38.2, C39.2, C40.2, C41.2, C43.2, C44.2, C45.2, C46.2, C47.2, C48.2, C49.2, C50.2, C51.2, C107.1, C108.1, C109.1, L6.2, R1.2, R3.2, R61.1, U1.L16 (VCC-DRAM), U1.M16 (VCC-DRAM), U1.N16 (VCC-DRAM), U1.P16 (VCC-DRAM), U1.P17 (VCC-DRAM), U1.R16 (VCC-DRAM), U1.T12 (VCC-DRAM), U1.T13 (VCC-DRAM), U1.T14 (VCC-DRAM), U1.T15 (VCC-DRAM), U1.U11 (VCC-DRAM), U2.A1 (VDDQ), U2.A8 (VDDQ), U2.B2 (VDD), U2.C1 (VDDQ), U2.C9 (VDDQ), U2.D2 (VDDQ), U2.D9 (VDD), U2.E9 (VDDQ), U2.F1 (VDDQ), U2.G7 (VDD), U2.H2 (VDDQ), U2.H9 (VDDQ), U2.K2 (VDD), U2.K8 (VDD), U2.N1 (VDD), U2.N9 (VDD), U2.R1 (VDD)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
VCC: 3.3V.1, C60.1, C61.2, C62.2, C63.2, C65.2, C66.2, C70.2, C71.2, C88.2, C121.1, C122.1, C127.1, D2.A, FET1.1 (G), FET3.3 (D), GPIO-1.3, L1.1, L9.2, LAN.AG, LAN.AY, R12.2, R13.1, R14.1, R17.1, R18.1, R19.2, R20.2, R26.1, R27.1, R28.1, R29.1, R30.1, R31.1, R32.1, R33.1, R34.1, R35.1, R43.2, RM1.1.2 (2), RM1.2.2 (2), RM1.3.2 (2), RM1.4.2 (2), U1.G7 (EPHY_VCC), U1.G10 (VDD_EFUSE), U1.G11 (VCC_USB), U1.G13 (VCC_IO), U1.G14 (VCC_IO), U1.G15 (VCC_IO), U1.H7 (VCC_PG), U1.H13 (VCC_IO), U1.H14 (VCC_IO), U1.J6 (HVCC), U1.J14 (VCC_IO), U1.J15 (VCC_PD), U4.1 (NC), U4.12 (VCC), U4.24 (NC), U4.34 (NC), U4.37 (VCC), U4.39 (NC), UEXT.1
VCC/2: 1.3V.1, C53.1, C54.1, C55.2, C56.2, C129.1, C130.1, L11.2, R77.1, U1.N8 (VDD_CPUX), U1.P6 (VDD_CPUX), U1.P7 (VDD_CPUX), U1.P8 (VDD_CPUX), U1.P9 (VDD_CPUX), U1.R6 (VDD_CPUX), U1.R7 (VDD_CPUX), U1.R8 (VDD_CPUX), U1.T6 (VDD_CPUX), U1.T7 (VDD_CPUX), U1.T8 (VDD_CPUX), U1.U6 (VDD_CPUX), U1.U9 (VDD_CPUX)
VCCINT: 1.1V_CPUS.1, C58.1, C59.2, C69.1, C104.1, R60.1, U1.J7 (VDD_CPUS), U1.J8 (VDD_CPUS), U1.M4 (RTC_VIO), U11.4 (VOUT)
VDD: 1.2V.1, C28.1, C29.2, C30.2, C31.2, C32.2, C115.1, C116.1, C117.1, L8.2, R67.1, U1.F8 (EPHY_VDD), U1.H10 (VDD_SYS), U1.J10 (VDD_SYS), U1.J11 (VDD_SYS), U1.J12 (VDD_SYS), U1.K10 (VDD_SYS), U1.K11 (VDD_SYS), U1.K12 (VDD_SYS), U1.L10 (VDD_SYS), U1.L11 (VDD_SYS), U1.L12 (VDD_SYS), U1.L13 (VDD_SYS), U1.L14 (VDD_SYS)
VDD-CPUFB: R82.1 (1.1), U1.T10 (VDD_CPUFB)
VDD-CPUFB1: C134.1, R77.2, R80.2, R82.2 (1.2)
VDD_EFUSEBP: C68.1, U1.H11 (VDD_EFUSEBP)
VPP: ANALOG.1, C73.2, C74.2, C119.1, C120.1, L9.1, R25.2, U1.G9 (V33_TV), U1.N3 (VCC_PLL), U1.V3 (AVCC), VR1.5 (VOUT)
VPS: R17.2, R21.1, U4.38 (NC)
X32KFOUT: GPIO-1.12, U1.P3 (X32KFOUT)
XTALI: C81.2, Q1.2, U1.K2 (X24MIN)
XTALO: C82.2, Q1.1, U1.K1 (X24MOUT)

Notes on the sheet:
MicroSD KART
32Gb (4096M x 8bit)
LEDs
Buttons
4G Bytes NAND Flash
Debug UART
32 GB NAND FLASH BELLEK
HDMI VIDEO ÇIKIŞ
USB-OTG
USB-HOSTs
Ethernet 100 MBIT
EXTRA PORT ÇIKIŞ PİNLERİ
DDR3 RAM BELLEK
PWR-STB
PWR-DRAM
PWRON/WORK
STANDBY
PWROFF
MODE
STATE
???
ANA SİSTEM REGULATORÜ
ALLWINNER H3 ANDROID 7 VE LINUX PC
MURAT IRKAN 2023 LINUX/ANDROID PC

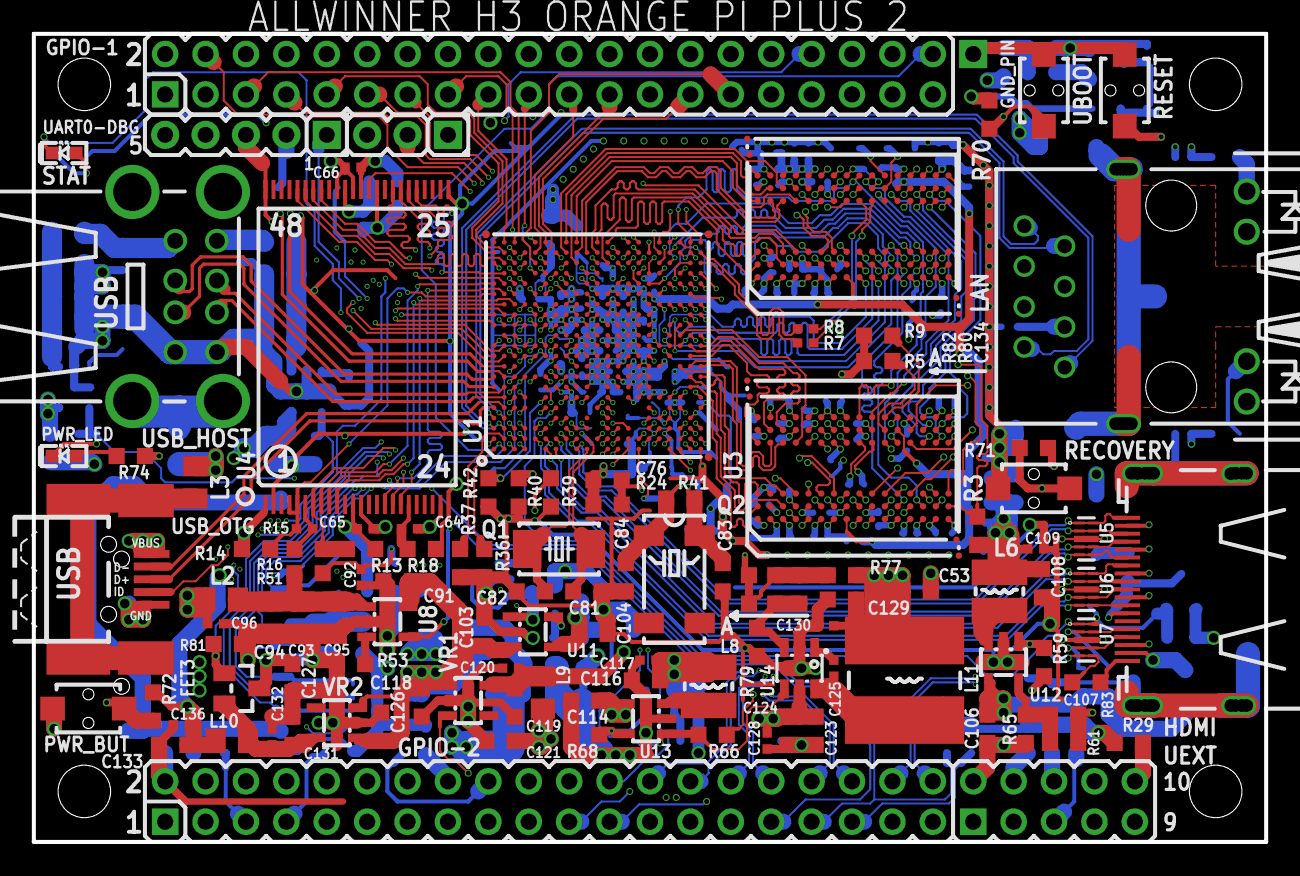
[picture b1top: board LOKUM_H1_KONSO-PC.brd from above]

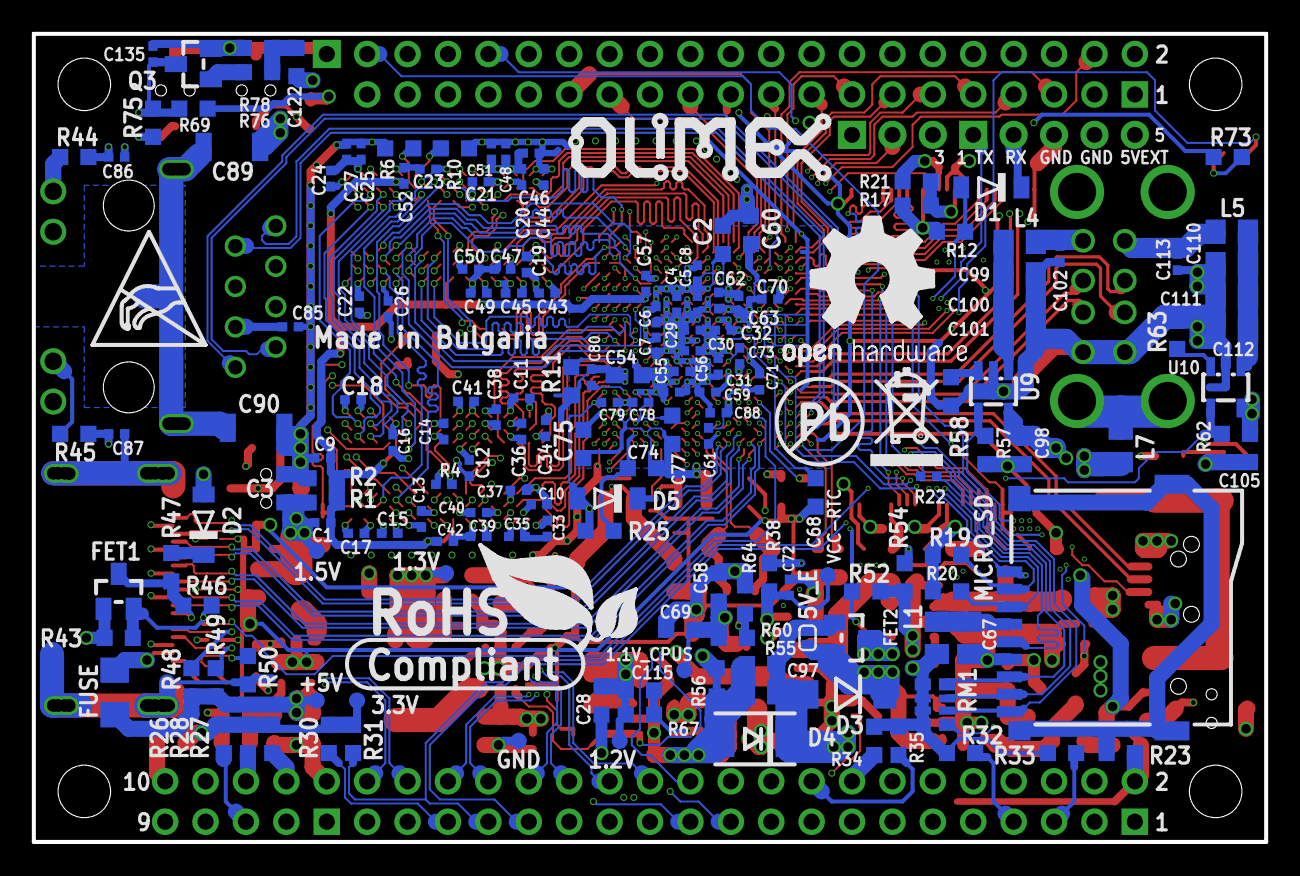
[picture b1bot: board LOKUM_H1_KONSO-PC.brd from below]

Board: 6 copper layers, 77.5 x 50.8 mm, 291 parts (175 on the bottom side), 296 nets.

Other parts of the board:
U$1: LOGO-OPENHARDWARE_8X8
U$8: OLIMEX1_V
U$9: PB
U$10: ESD_SYMBOL
U$11: RECYCLE_BIN1/8
U$12: ROHS

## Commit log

2024-04-25 LOKUM ARM OYUN KONSOLU
    TASARIM DEMOSU.
    ARM CPU: ALLWINNER H3 VEYA ROKCHIP RK3288
    OS: ANDROID VE LINUX
2024-04-26 LOKUM -KONSOL SEFFAF
2024-04-30 OYUN KONSOLU LOKUM ( RASPBERRY PI VE ALLWINNER H3)
    MURAT IRKAN 2023-24
    REV.A
2024-05-01 LOKUM ANDROID(LINUX) KONSOL
    ALLWINNER H3 VEYA RASPBERRY PI 3-4
2024-05-05 ALLWINNER H3 3D ŞASE-KIRMIZI-MAVİ
    3D TASARIM DOSYASI SOLIDWORKS 2018
2024-05-05 AUTODESK EAGLE H3 ŞEMA MINI-PC
    REV.B 2023
2024-05-05 AUTODESK EAGLE ALLWINNER H3 PC ŞEMASI
    REV.B 2023 MURAT IRKAN
2024-05-17 ANDROID 11 KONSOL OYUNU:YILAN DEMO
    MURAT IRKAN 14-07-2023
    MICROSOFT VISUAL STUDYO 2022
2024-05-18 LOKUM R-RK3188 ARM CPU
    REV.C
2024-05-19 ROCKCHIP-RK3188 KONSOL-PC
    REV.A 2023
2024-05-23 ARM KONSOL
2024-05-23 LOKUM KONSOL:ALWINNER H3 ARM CPU ŞEMA
    REV.A
    2023 MURAT IRKAN
2024-05-23 LOKUM KONSOL 3D-SOLIDWORKS versiyon 2018
    LOKUM H1 VE R1 ARM ANDROID-LINUX KONSOL PROJESİ
    2023-24
2024-05-23 LOKUM-R2 KONSOL
2024-05-23 KONSOL 3D-TASARIM(SOLIDWORKS & AUTOCAD)
    PROTOTIP A VE B
2024-05-24 ALLWINNER-H3 PC-KONSOL
    REV.B
2024-05-24 LOKUM KONSOL RK3288 ARM-CPU
    REV.A:2024-02
2024-05-25 LOKUM H1 (CPU:ALLWINNER H3 2GB VE 4GB DDR3 1866)
    REV.B
2024-05-28 ALLWINNER H3 ARM CPU 2GB DDR3 BELLEK PCB
    REV.A VE B
2024-05-29 LOKUM R3 RK3588 ARM-CPU 8 ÇEKİRDEK 16GB DDR5 RAM
    DEMO TASARIM.REV.A
    MURAT IRKAN 2024-04
2024-05-30 LOKUM-H1 + 3D TASARIM
    ANDROID 7.0 VE 7.1
2024-05-30 LOKUM-PC/KONSOL SARI-MAVİ(3D SOLIDWORKS-AUTOCAD)
2024-05-31 ORANGE PC PLUS 2E
2024-06-07 RK3328 ARM KONSOL/PC
    REFERANS A:
2024-06-09 LOKUM -H1 ARM ANDROID 7 KONSOL
    AUTODESK EAGLE SİSTEM TASARIM REV.B
    ----------------------------------------------
    DDR3 SAMSUNG 2 GB
2024-06-09 NINTENDO_MINI_KONSOL
2024-08-17 LOKUM ANDROID(7.1) KONSOL
    MURAT IRKAN ALLWINNER H3 1.6GH/z ARM CPU
    REV.A VE B
2024-08-18 LOKUM KONSOL KUTUSU(3D STEP DOSYA)
    SOLIDWORKS 2018 STEP DOSYA 3D ŞASE ATSARIMI DENEME
2024-08-18 LOKUM KONSOL ANDROID 7.1(DIPTRACE 2024 DEVRE PRG.)
    DIPTRACE 2024 VERSIYON DEVRE ŞEMASI
    1.LOKUM ALLWINNER H3 ARM İŞLEMÇİ
    2.DDR3 SAMSUNG BELLEK
    3.1000 GIGABIT LAN
    4.HDMI 4K VIDEO ÇIKIŞ
    USB A VE B - HARICI DISK VE 12v ADAPTOR GİRİŞİ.
2024-08-18 SAMSUNG DDR3 1600 MHZ SDRAM
2024-08-18 LOKUM_ARM_OYUN_KONSOLU(ANDROID 7.1)
    MURAT IRKAN 2023/24
    REV.A
    SAMSUNG 4G DDR3 1600/ 1866 mhz
2024-08-22 OKU.md
2024-08-24 LOKUM MINI + 3D TASARIM DOSYASI (SOLIDWORKS 2018)
    1.ALLWINNER A33 ARM CPU DIPTRACE VE EAGLE ŞEMA
    2.SOLIDWORKS 3D TASARIM MINI KONSOL
    3.ALLWINNER H3 ARM CPU
    4.HYNIX LPDDR3 1600/1866 MHERTZ
2024-09-14 LOKUM ALLWINNER A33 MINI-KONSOL
    AUTODESK EAGLE SİSTEM DEVRE TASARIMI REV.C
